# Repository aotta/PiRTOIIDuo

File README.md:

# PiRTOIIDuo
New PiRTO multicart for Intellivision with JLP support, based on Raspberry Pico2 

PiRTO II DUO is the new version of my PiRTO multicart DIY yourself based now on a Raspberry Pi Pico2 for using double RAM.

This version support Intellivision bin+cfg games, including the JLP acceleration and savegames features.
It works with all games i testes since now, except for "Onion" (it's a big rom and i think it will need next pico3 ;) )

changelog:
v.1.00 - initial release

v.1.01 - bugfix in parsing cfg

v.1.02 - added parsing for "jlp_accel" params, improved overclock for "Onion"

v.1.03 - increaded RAMSIZE to 0x4000 from 0x2000, bug fixed for YM-Player

Kicad project and gerbers files for the pcb are in the PCB folder, you need only a diode, a push buttons for resetting the cart if needed or want restart, and the micro SDCard holder. 
Add you pico2, and flash the firmware ".uf2" in the Pico by connecting it while pressing button on Pico and drop it in the opened windows on PC.
Use the SDCard to store "BIN" and "CFG“ files  into.

3D files for shell coming soon!

More info on AtariAge forum: [https://forums.atariage.com/](https://forums.atariage.com/topic/386798-pirto-ii-duo-powered-by-pico2-with-jlp-support/)

Even if the diode should protect your console, **DO NOT CONNECT PICO WHILE INSERTED IN A POWERED ON CONSOLE!**
You can use any schottky diode, i usually put 1n4148

## Credits
This upgrade is dedicated to Mariella, with love and gratitude for trusting me and encouraging me to never give up

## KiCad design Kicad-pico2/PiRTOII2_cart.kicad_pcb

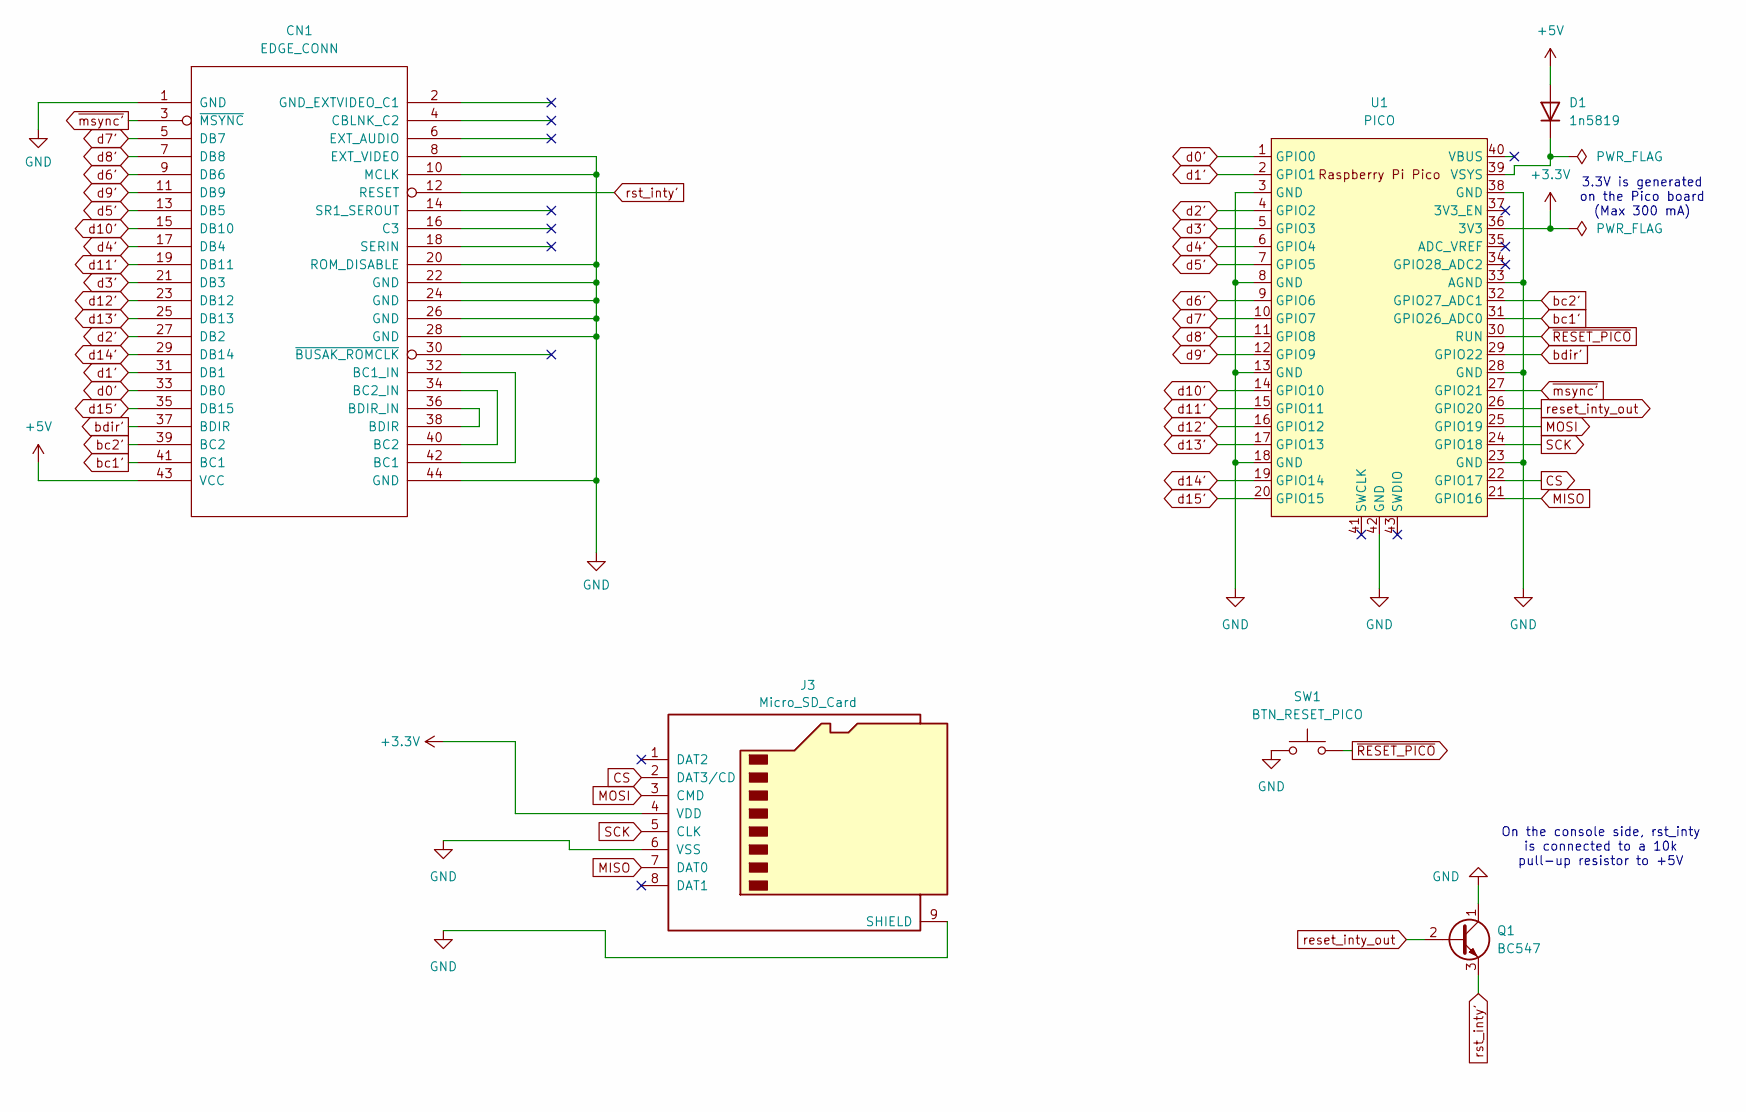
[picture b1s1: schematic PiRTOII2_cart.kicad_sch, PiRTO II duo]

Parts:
CN1: EDGE_CONN; Intellivision_Edge_Connector
D1: 1n5819; D_DO-41_SOD81_P10.16mm_Horizontal
J3: Micro_SD_Card; J_SD_Card-micro_socket_A
Q1: BC547; TO-92L_HandSolder
SW1: BTN_RESET_PICO; SW_Tactile_SPST_Angled_PTS645Vx83-2LFS
U1: PICO; RPi_Pico_SMD_TH

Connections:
+3.3V: J3.4 (VDD), U1.36 (3V3)
+5V: CN1.43 (VCC), D1.2 (A)
CS: J3.2 (DAT3/CD), U1.22 (GPIO17)
GND: CN1.1 (GND), CN1.8 (EXT_VIDEO), CN1.10 (MCLK), CN1.20 (ROM_DISABLE), CN1.22 (GND), CN1.24 (GND), CN1.26 (GND), CN1.28 (GND), CN1.44 (GND), J3.6 (VSS), J3.9 (SHIELD), Q1.1 (C), SW1.1, U1.3 (GND), U1.8 (GND), U1.13 (GND), U1.18 (GND), U1.23 (GND), U1.28 (GND), U1.33 (AGND), U1.38 (GND), U1.42 (GND)
MISO: J3.7 (DAT0), U1.21 (GPIO16)
MOSI: J3.3 (CMD), U1.25 (GPIO19)
unnamed: CN1.32 (BC1_IN), CN1.42 (BC1)
unnamed: CN1.34 (BC2_IN), CN1.40 (BC2)
unnamed: CN1.36 (BDIR_IN), CN1.38 (BDIR)
unnamed: D1.1 (K), U1.39 (VSYS)
SCK: J3.5 (CLK), U1.24 (GPIO18)
bc1': CN1.41 (BC1), U1.31 (GPIO26_ADC0)
bc2': CN1.39 (BC2), U1.32 (GPIO27_ADC1)
bdir': CN1.37 (BDIR), U1.29 (GPIO22)
d0': CN1.33 (DB0), U1.1 (GPIO0)
d1': CN1.31 (DB1), U1.2 (GPIO1)
d2': CN1.27 (DB2), U1.4 (GPIO2)
d3': CN1.21 (DB3), U1.5 (GPIO3)
d4': CN1.17 (DB4), U1.6 (GPIO4)
d5': CN1.13 (DB5), U1.7 (GPIO5)
d6': CN1.9 (DB6), U1.9 (GPIO6)
d7': CN1.5 (DB7), U1.10 (GPIO7)
d8': CN1.7 (DB8), U1.11 (GPIO8)
d9': CN1.11 (DB9), U1.12 (GPIO9)
d10': CN1.15 (DB10), U1.14 (GPIO10)
d11': CN1.19 (DB11), U1.15 (GPIO11)
d12': CN1.23 (DB12), U1.16 (GPIO12)
d13': CN1.25 (DB13), U1.17 (GPIO13)
d14': CN1.29 (DB14), U1.19 (GPIO14)
d15': CN1.35 (DB15), U1.20 (GPIO15)
reset_inty_out: Q1.2 (B), U1.26 (GPIO20)
rst_inty': CN1.12 (RESET), Q1.3 (E)
~RESET_PICO: SW1.2, U1.30 (RUN)
~msync': CN1.3 (~MSYNC), U1.27 (GPIO21)

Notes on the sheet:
3.3V is generated on the Pico board (Max 300 mA)
On the console side, rst_inty is connected to a 10k pull-up resistor to +5V

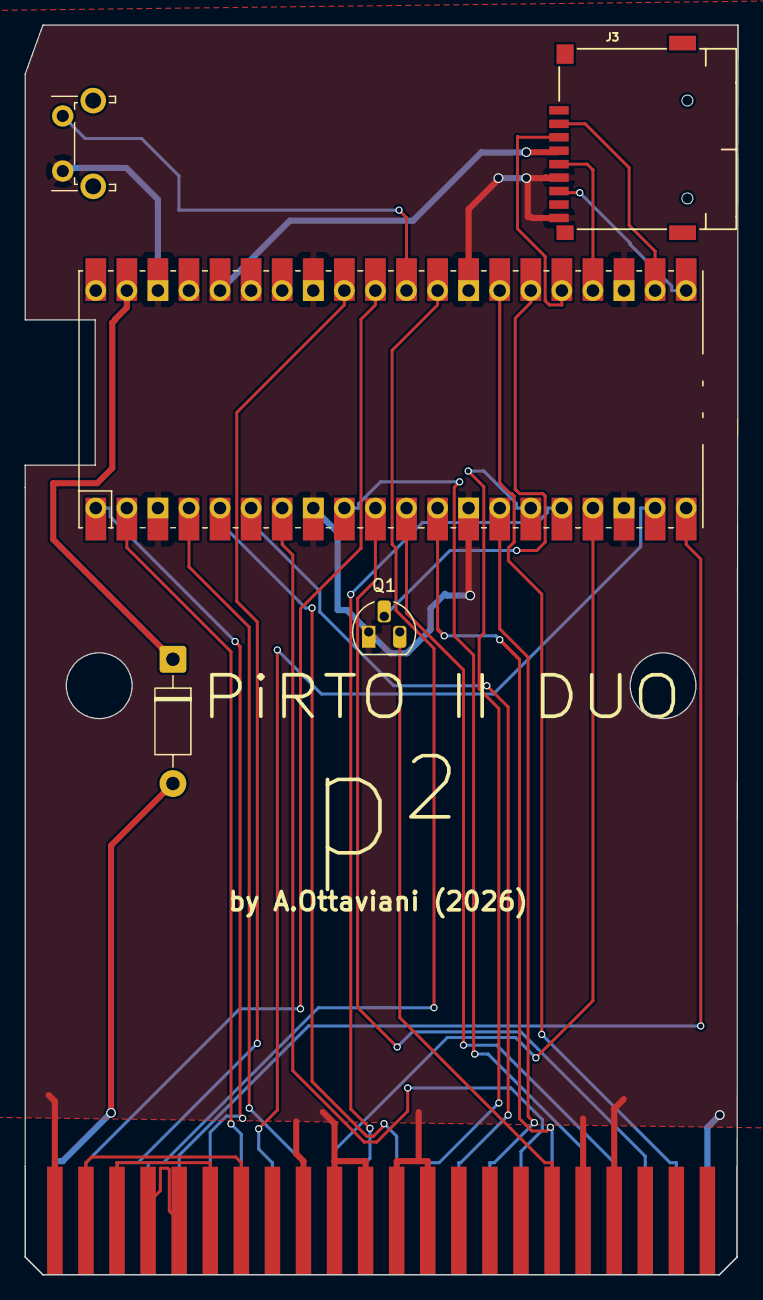
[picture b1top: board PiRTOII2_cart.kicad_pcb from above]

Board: 2 copper layers, 58.3 x 102.1 mm, 6 parts (0 on the bottom side), 34 nets.

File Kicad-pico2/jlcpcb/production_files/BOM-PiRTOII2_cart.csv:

Comment,Designator,Footprint,LCSC,Quantity
Micro_SD_Card,J3,J_SD_Card-micro_socket_A,C393941,1
BTN_RESET_PICO,SW1,SW_Tactile_SPST_Angled_PTS645Vx83-2LFS,,1
1n5819,D1,D_DO-41_SOD81_P10.16mm_Horizontal,,1
BC547,Q1,TO-92L_HandSolder,,1
PICO,U1,RPi_Pico_SMD_TH,,1
EDGE_CONN,CN1,Intellivision_Edge_Connector,,1

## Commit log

2025-12-28 added 3d files for shell
2025-12-29 1.01 bug fix
    fixed parsing cfg file for skipping "build_date" row
2025-12-29 v.1.01 bug fix
    fixed cfg parsing "build_date" row
2026-01-03 v.1.02 bugfix
2026-01-26 added enh. version by XAD-nightfall
2026-02-12 Add files via upload
    removed some debug print left in code
2026-04-25 Ram increased to 32kb - bug fix for YM-Player
2026-04-25 V.1.03
    increaded from 0x2000, bug fixed for YM-Player
